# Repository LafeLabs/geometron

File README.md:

# Geometron: Geometric Metalanguage

Geometron finally gets its own space on here, since it's clearly a separate project now from Action Geometry.  Many bifurcations need to happen now to make it clearer which project is which and what the applications are.  

Geometron is a language of glyphs, which describe geometric concepts which can be interpreted both by humans and machines.  It is intended to be universally applicable across all human cultures and languages and also across all physical machine architectures both present and future.  

The political and philosophical goal of Geometron is to eliminate layers in technology which are currently controlled by various priest classes, freeing technology and giving people more power over their machines.  

This is part of the larger system of knowledge I am building, which includes the Roctal system for physical data encoding, the Action Geometry system of physical constructions, Trash Magic philosophy and technology and art, and several other components.  So all the various commands in the instruction set that this language is built on as well as the more complex components which are built up recursively have octal addresses which can be expressed using Roctal.  

### [0. Motivation Introduction](markdown/markdown_paper.md)

### [0.01 General Language Structure](what_exactly_is_geometron.md)

### [1. Fourfold Symmetry Introduction](4fold1/fourfold_symmetry.md)

### [2. Glyph of Glyphs](glyph_of_glyphs/glyph_of_glyphs.md)

### [3. Recursion: A. Square](recursionSquare/recursionSquare.md)

### [4. Scaling by 2: Halving and Doubling](scaling_by_two/scaling_by_two.md)

### [5. Angle Bisection and Scaling by Square Root of 2](square_root_2/square_root_2.md)

### [6. Glyph to Text, Text to Glyph](keyboardMapping/keyboardmapping.md)

### [7. Spelling: Glyph and Glyph Table Creation](glyphTableEdit/glyphTableEdit.md)

### [Meta-Company](meta-company.md)

### 8. Threefold and Sixfold Symmetries

### 9. Fivefold Symmetries

### 10. Detailed Study of Address Space and Roctal Encoding

### 11. Font Creation and Use

### State Stack

### 12. Adding the Third Dimension

### 13. Image Interaction for Art and Communication

### image stack

### 14. Building Systems and Implementation

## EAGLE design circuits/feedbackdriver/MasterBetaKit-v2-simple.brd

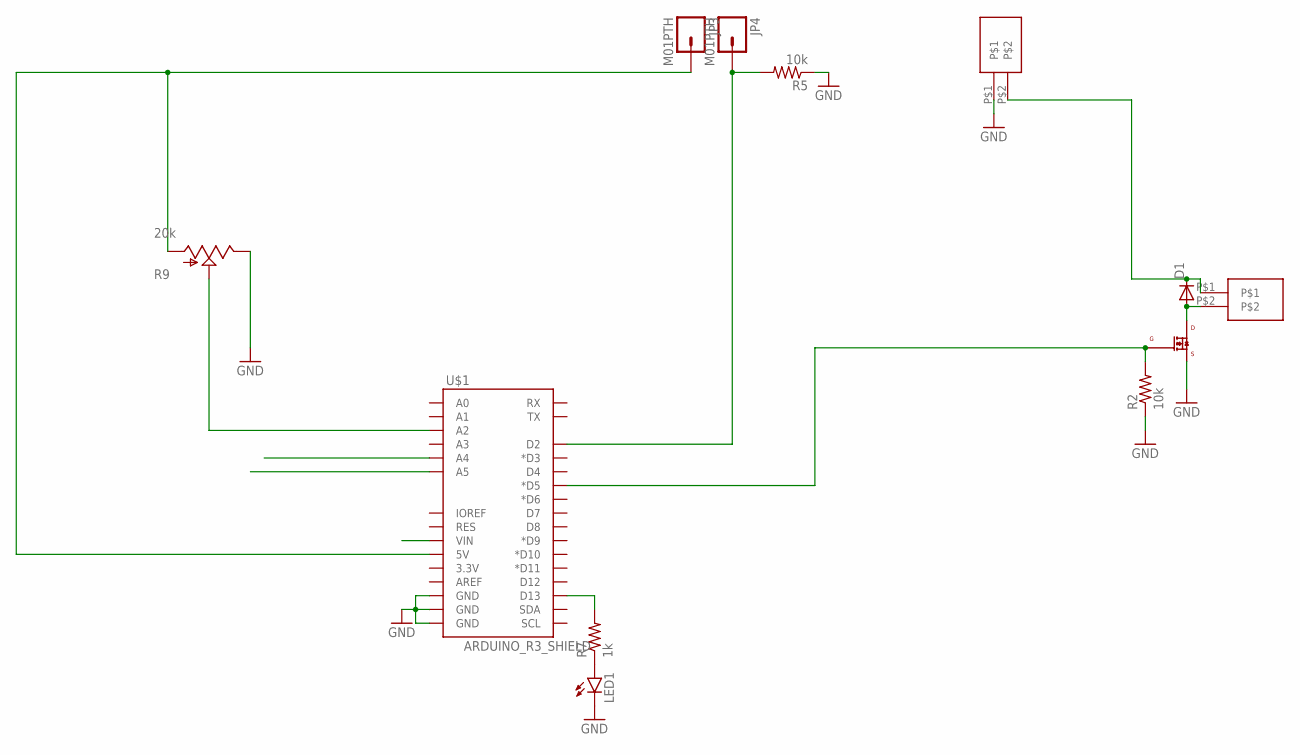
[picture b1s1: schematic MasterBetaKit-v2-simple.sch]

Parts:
D1: DIODE-DO-214AC; DO-214AC
JP3, JP4: M01PTH; 1X01
LED1: LED-3MM-NO_SILK; LED3MM-NS
R2, R5: 10k; R0603
R7: 1k; R0603
R9: 20k; ALPS_POT_KIT
U$1: ARDUINO_R3_SHIELD; UNO_R3_SHIELD
U$2: IRLML0060; SOT-23
U$6: SPRING-TERMINAL
X3: SPRING-TERMINAL

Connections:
5V: JP3.1, R9.P$3 (A), U$1.5V
BUTTON: JP4.1, R5.2, U$1.D2
CL: U$1.A5
DA: U$1.A4
GND: LED1.K (C), R2.1, R5.1, R9.P$1 (E), U$1.GND@0 (GND), U$1.GND@1 (GND), U$1.GND@2 (GND), U$2.2 (SOURCE), X3.P$1
unnamed: R2.2, U$1.D5 (*D5), U$2.1 (GATE)
unnamed: D1.A, U$2.3 (DRAIN), U$6.P$2
unnamed: LED1.A, R7.1
unnamed: R7.2, U$1.D13
unnamed: R9.P$2 (S), U$1.A2
X4: D1.C, U$6.P$1, X3.P$2

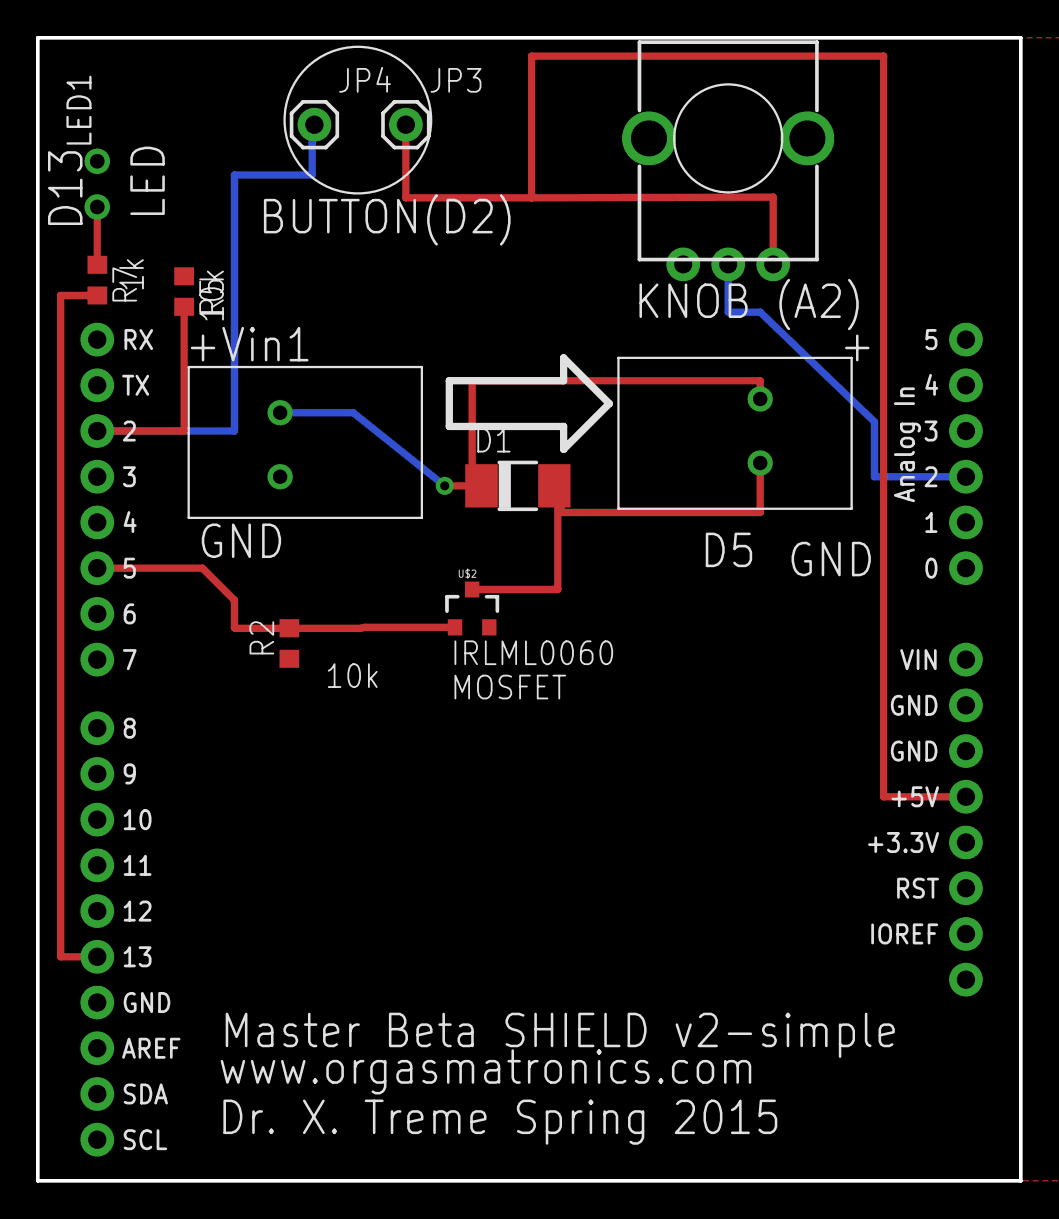
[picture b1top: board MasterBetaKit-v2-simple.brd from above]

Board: 2 copper layers, 54.6 x 63.5 mm, 12 parts (0 on the bottom side), 9 nets.

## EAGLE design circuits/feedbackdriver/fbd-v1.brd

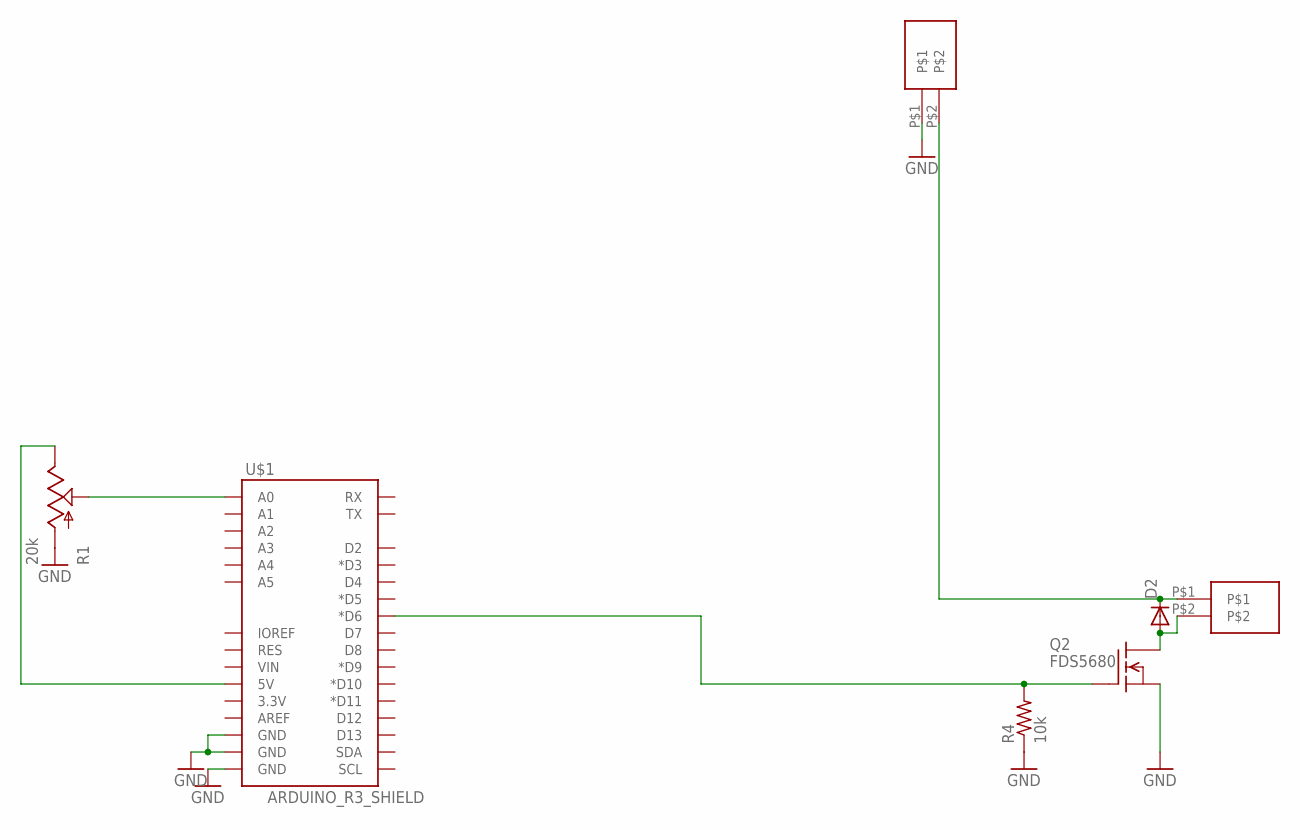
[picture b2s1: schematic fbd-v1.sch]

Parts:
D2: DIODE-DO-214AC; DO-214AC
Q2: FDS5680; SO-8
R1: 20k; ALPS_POT_KIT
R4: 10k; R0603
U$1: ARDUINO_R3_SHIELD; UNO_R3_SHIELD
X3, X5: SPRING-TERMINAL

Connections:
GND: Q2.1 (S), Q2.2 (S), Q2.3 (S), R1.P$3 (A), R4.1, U$1.GND@0 (GND), U$1.GND@1 (GND), U$1.GND@2 (GND), X3.P$1
unnamed: R1.P$2 (S), U$1.A0
unnamed: R1.P$1 (E), U$1.5V
unnamed: D2.A, Q2.5 (D), Q2.6 (D), Q2.7 (D), Q2.8 (D), X5.P$2
unnamed: Q2.4 (G), R4.2, U$1.D6 (*D6)
X4: D2.C, X3.P$2, X5.P$1

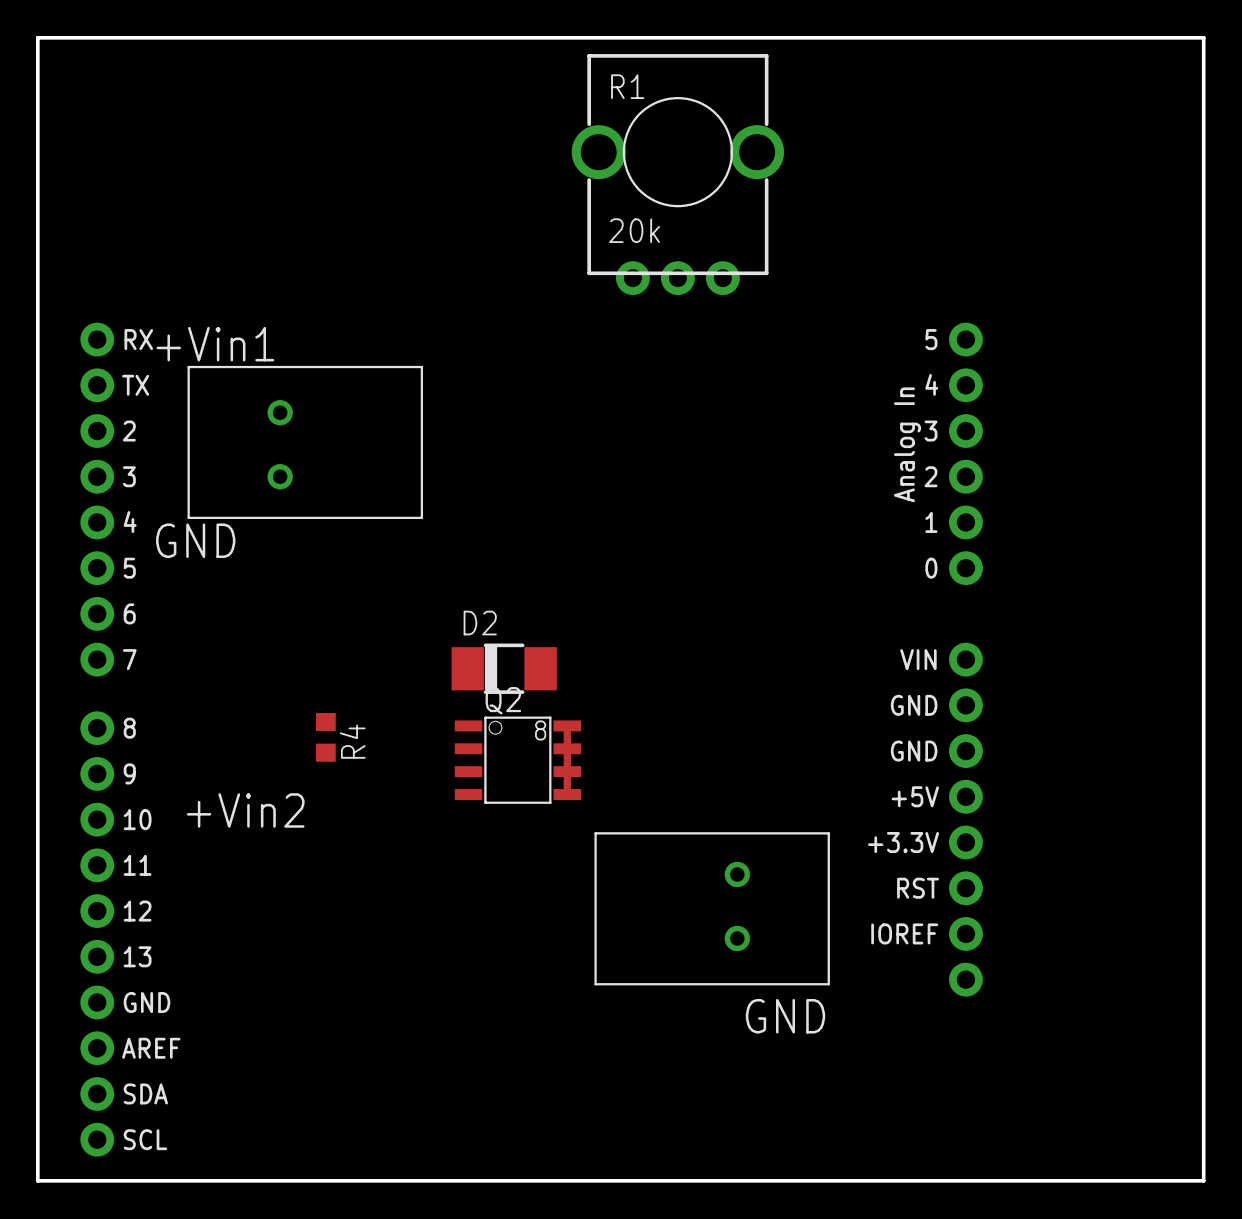
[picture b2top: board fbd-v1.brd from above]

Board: 2 copper layers, 64.8 x 63.5 mm, 7 parts (0 on the bottom side), 6 nets.

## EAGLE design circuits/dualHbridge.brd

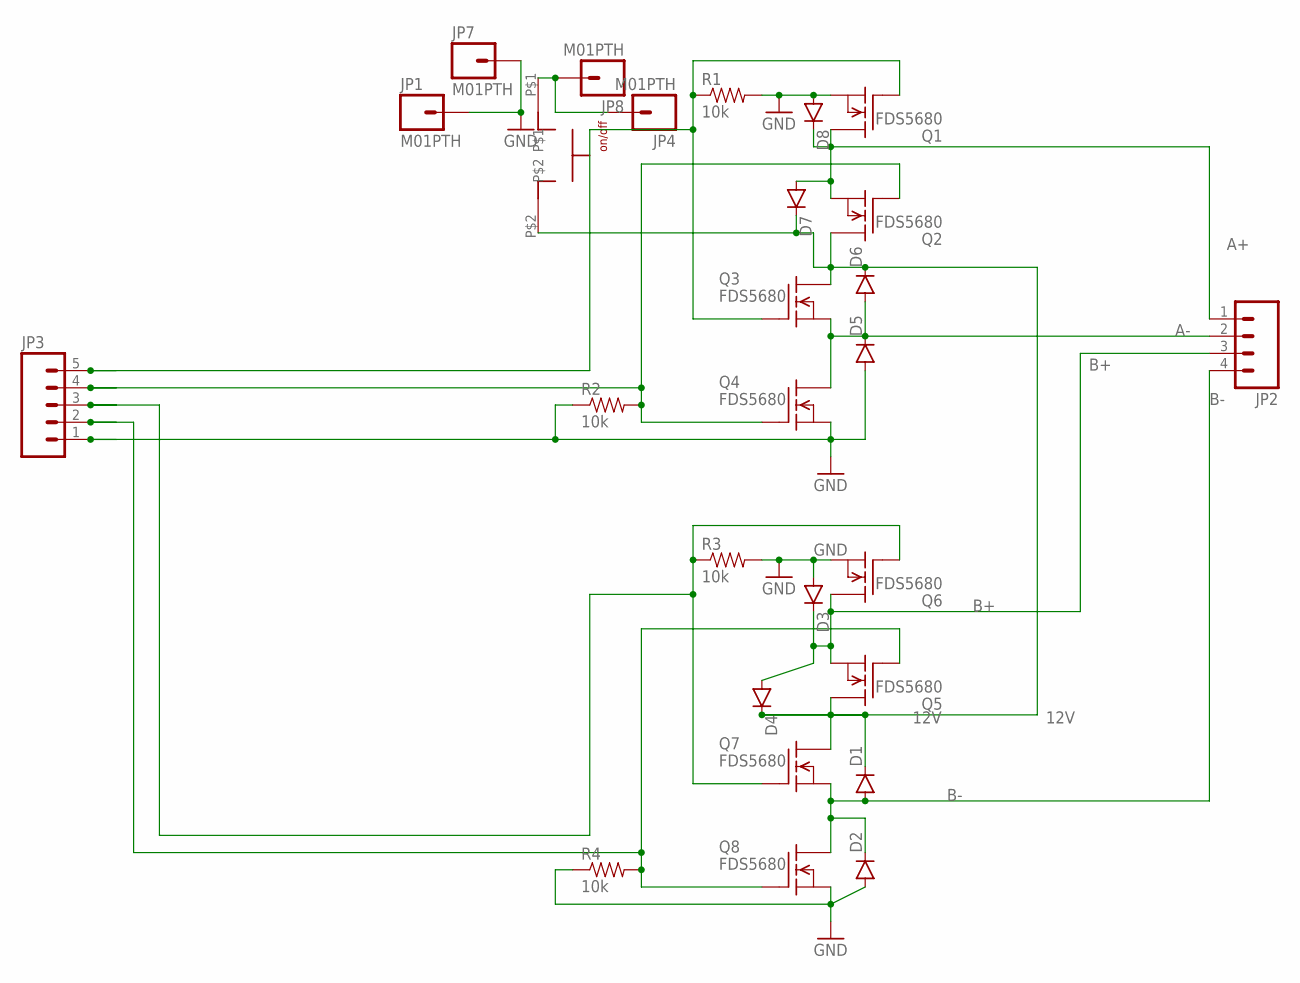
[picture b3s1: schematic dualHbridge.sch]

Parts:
D1, D2, D3, D4, D5, D6, D7, D8: DIODEKIT2; DIODE-1N4001-KIT
JP1, JP4, JP7, JP8: M01PTH; 1X01
JP2: M04LONGPADS; 1X04_LONGPADS
JP3: M05PTH; 1X05
Q1, Q2, Q3, Q4, Q5, Q6, Q7, Q8: FDS5680; SO-8
R1, R2, R3, R4: 10k; 0603-RES
U$5: CW182-ND

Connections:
12V: D1.C, D4.C, D6.C, D7.C, Q2.5 (D), Q2.6 (D), Q2.7 (D), Q2.8 (D), Q3.5 (D), Q3.6 (D), Q3.7 (D), Q3.8 (D), Q5.5 (D), Q5.6 (D), Q5.7 (D), Q5.8 (D), Q7.5 (D), Q7.6 (D), Q7.7 (D), Q7.8 (D), U$5.P$2; also elsewhere on the board
A+: D7.A, D8.C, JP2.1, Q1.5 (D), Q1.6 (D), Q1.7 (D), Q1.8 (D), Q2.1 (S), Q2.2 (S), Q2.3 (S)
A-: D5.C, D6.A, JP2.2, Q3.1 (S), Q3.2 (S), Q3.3 (S), Q4.5 (D), Q4.6 (D), Q4.7 (D), Q4.8 (D)
B+: D3.C, D4.A, JP2.3, Q5.1 (S), Q5.2 (S), Q5.3 (S), Q6.5 (D), Q6.6 (D), Q6.7 (D), Q6.8 (D)
B-: D1.A, D2.C, JP2.4, Q7.1 (S), Q7.2 (S), Q7.3 (S), Q8.5 (D), Q8.6 (D), Q8.7 (D), Q8.8 (D)
GND: D2.A, D3.A, D5.A, D8.A, JP1.1, JP3.1, JP7.1, Q1.1 (S), Q1.2 (S), Q1.3 (S), Q4.1 (S), Q4.2 (S), Q4.3 (S), Q6.1 (S), Q6.2 (S), Q6.3 (S), Q8.1 (S), Q8.2 (S), Q8.3 (S), R1.2, R2.1, R3.2, R4.1; also elsewhere on the board
unnamed: JP3.5, Q1.4 (G), Q3.4 (G), R1.1
unnamed: JP3.4, Q2.4 (G), Q4.4 (G), R2.2
unnamed: JP3.3, Q6.4 (G), Q7.4 (G), R3.1
unnamed: JP3.2, Q5.4 (G), Q8.4 (G), R4.2
unnamed 14: JP4.1, JP8.1, U$5.P$1; also elsewhere on the board

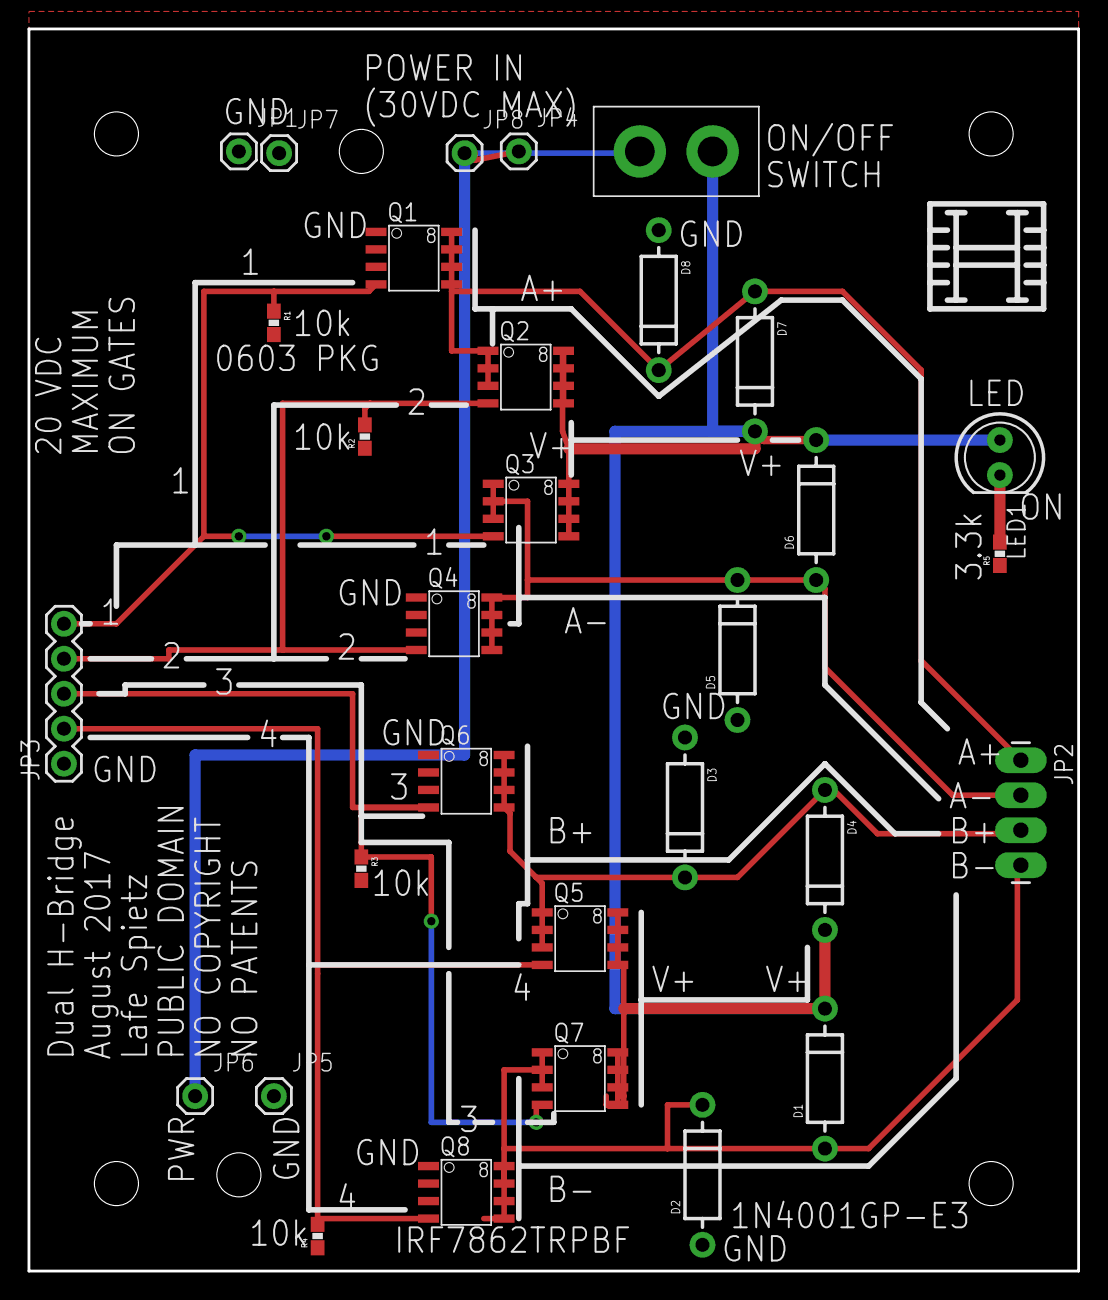
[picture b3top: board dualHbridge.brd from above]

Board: 2 copper layers, 76.2 x 90.2 mm, 31 parts (0 on the bottom side), 12 nets.

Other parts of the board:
JP5, JP6: M01PTH; 1X01
LED1: LED5MM
R5: 3.3k; 0603-RES

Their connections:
12V: LED1.A; also elsewhere on the board
GND: JP5.1, R5.1; also elsewhere on the board
unnamed: LED1.K, R5.2
unnamed 14: JP6.1; also elsewhere on the board

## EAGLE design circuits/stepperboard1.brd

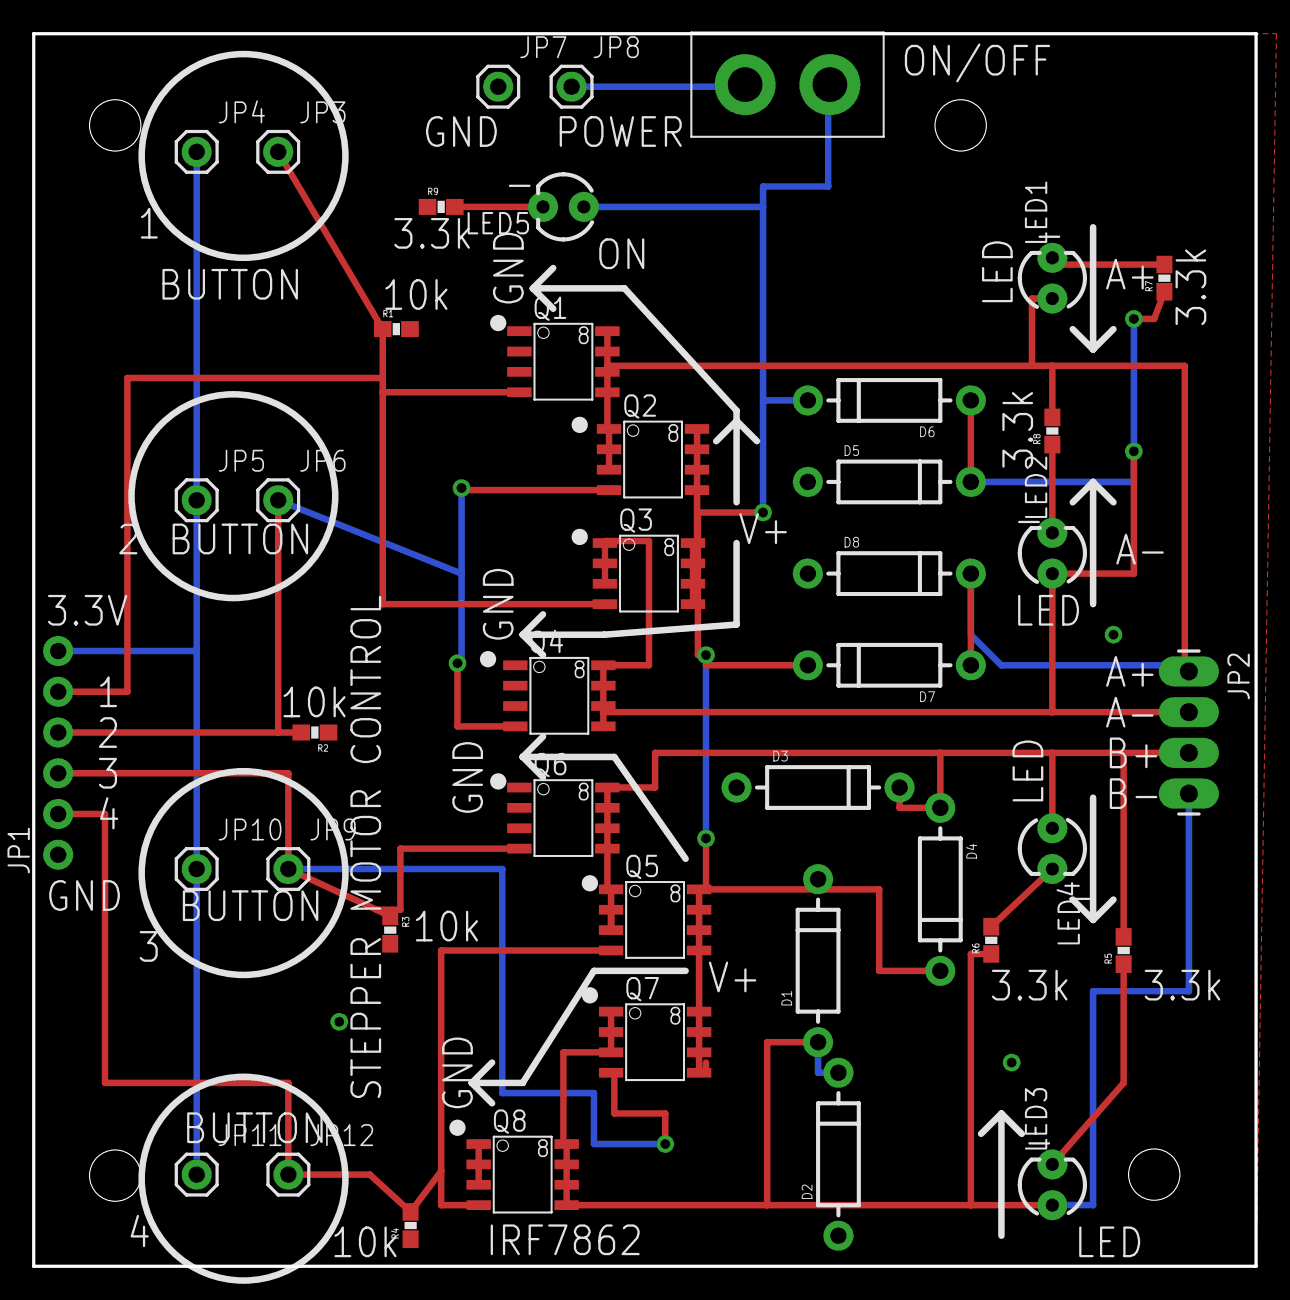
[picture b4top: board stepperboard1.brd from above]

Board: 2 copper layers, 76.2 x 76.8 mm, 43 parts (0 on the bottom side), 17 nets.

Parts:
D1, D2, D3, D4, D5, D6, D7, D8: DIODE-1N4001-KIT
JP1: 1X06_NO_SILK
JP2: 1X04_LONGPADS
JP3, JP4, JP5, JP6, JP7, JP8, JP9, JP10, JP11, JP12: M01PTH; 1X01
LED1, LED2, LED3, LED4, LED5: LED3MM
Q1, Q2, Q3, Q4, Q5, Q6, Q7, Q8: FDS5680; SO-8
R1, R2, R3, R4: 10k; 0603-RES
R5, R6, R7, R8, R9: 3.3k; 0603-RES
U$5: CW182-ND

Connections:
12V: D1.C, D4.C, D6.C, D7.C, LED5.A, Q2.5, Q2.6, Q2.7, Q2.8, Q3.5, Q3.6, Q3.7, Q3.8, Q5.5, Q5.6, Q5.7, Q5.8, Q7.5, Q7.6, Q7.7, Q7.8, U$5.P$2
A+: D7.A, D8.C, JP2.1, LED1.A, Q1.5, Q1.6, Q1.7, Q1.8, Q2.1, Q2.2, Q2.3, R8.2
A-: D5.C, D6.A, JP2.2, LED2.A, Q3.1, Q3.2, Q3.3, Q4.5, Q4.6, Q4.7, Q4.8, R7.1
B+: D3.C, D4.A, JP2.3, LED4.A, Q5.1, Q5.2, Q5.3, Q6.5, Q6.6, Q6.7, Q6.8, R5.2
B-: D1.A, D2.C, JP2.4, LED3.A, Q7.1, Q7.2, Q7.3, Q8.5, Q8.6, Q8.7, Q8.8, R6.1
GND: D2.A, D3.A, D5.A, D8.A, JP1.1, JP7.1, Q1.1, Q1.2, Q1.3, Q4.1, Q4.2, Q4.3, Q6.1, Q6.2, Q6.3, Q8.1, Q8.2, Q8.3, R1.2, R2.1, R3.2, R4.1, R9.1
unnamed: LED1.K, R7.2
unnamed: JP1.5, JP3.1, Q1.4, Q3.4, R1.1
unnamed: JP1.4, JP6.1, Q2.4, Q4.4, R2.2
unnamed: LED2.K, R8.1
unnamed: LED3.K, R5.1
unnamed: LED4.K, R6.2
unnamed: JP1.3, JP9.1, Q6.4, Q7.4, R3.1
unnamed: JP1.2, JP12.1, Q5.4, Q8.4, R4.2
unnamed: JP8.1, U$5.P$1
unnamed: LED5.K, R9.2
V3.3: JP1.6, JP4.1, JP5.1, JP10.1, JP11.1

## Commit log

2016-12-20 read me fleshed out a bit
2016-12-20 writing a actual document on fourfold symmetry
2016-12-20 added standalone app for just moving cursor, documented it
2016-12-20 added link from read me to fourfold section
2016-12-20 finished a draft of fourfold symmetry section
2016-12-20 added links to code at the end
2016-12-20 fixed directory name in link
2016-12-20 made links work properly connected it all together with read
2016-12-20 glyph of glyphs section mostly done
2016-12-20 added many sections to read me to be filled out next
2016-12-20 added doubling stuff and finished draft of recursion section
2016-12-20 not even sure what happened woke from nap
2016-12-21 added license
2016-12-21 added sqrt(2) stuff
2016-12-21 root 2 mostly done but need a ton more examples and explanation of the math
2016-12-22 added to keyboard mapping section, sketched out Root Magic Table
2016-12-22 clarified address bullet list with more ALL CAPS
2016-12-23 putting font together, finished 0300s table
2016-12-23 shape tables and font now done, ready for next step
2016-12-24 going from integer arrays to text works, but keyboard mode needs work, thought
2016-12-24 dropped the variable currentGlyph[] completely, using currentGlyphString for all, WORKS!!!!
2016-12-25 I can now edit a manuscript! The whole system appears to work now.
2016-12-25 made some more neat stuff in "manuscript"
2016-12-28 played with shapes, made new shapes, updated key map graphics
2016-12-29 ascii table ready to print
2016-12-29 cartoons explaining cursor in printable pdf
2016-12-30 scroll is a document to document itself, now has keys on spelling
2016-12-30 standalone app works now with geometron intro book--scroll1
2016-12-30 moved stuff around started mapping
2016-12-31 crowd funding strategy document
2017-01-01 image table works position stack works, root magic works
2017-01-01 ROOT MAGIC APOCALYPSE
2017-01-02 more documentation as art
2017-01-02 added timestamp to screenshot saver and more docs to function doc
2017-01-02 longbridgepark
2017-01-02 more documentation of octal, roctal
2017-01-03 an actual distribution for other people
2017-01-04 played with logarithmic spirals based on different generators
2017-01-05 crowd fund plan, more random bits
2017-01-05 updated ascii table to have roctal
2017-01-05 made pdfs with roctal youtube url stubs to be filled in by hand after printing
2017-01-06 read laminated code, links successfuly to youtube
2017-01-07 added some ideas on crowd fund
2017-01-07 printable scannable roctal codes for tale and lore for root2spiral tablet
2017-01-12 random tiny updates
2017-01-12 storyboarded the video
2017-01-14 more on video plans
2017-01-15 arduino control of trash robot
2017-01-20 added roctal code for geometron javascript page
2017-01-20 added a html sandbox to geometron repository
2017-01-21 made a js library and it works! i can now attempt to communicate with "normals"
2017-01-21 using processing to convert text to other text
2017-01-29 xml super apocalypse
    rewriting the entire geometron system in xml, attempting to break free
    of specific computer languages, fix stupid ascii problems i had
2017-01-29 xml is a fucking pile of steaming shit
    after 24 hours wasted on xml it is clear this solves no problems and
    adds several. going back to .txt in all cases
2017-01-29 xml is a piece of shit, moving back to all txt
    xml solves minimal issues and adds many, is clearly shit
2017-01-30 converted to txt then from txt to js, put that in library
2017-01-31 added manual conversion from text commands to octal commands
2017-03-20 Documenting the whole project in a markdown doc, not sure where to put this, need to move it somewhere
2017-03-21 moving bits around in main markdown docs
2017-03-21 updating documents on geometron pointing to the Project
2017-03-22 small tweaks here...
2017-04-23 trash2 is the current trash printer control code
2017-04-28 code updated for trash printer
2017-04-30 working on the crowd fund
2017-04-30 working on crowd fund video script
2017-05-16 successfully ported geometron into python! all with .SVG format output
2017-05-17 python geometron is now really working
2017-05-18 total recursion!!!!!
2017-05-18 fixed tab in textarea
2017-06-02 working with python to improve work flow with byte code and libraries
2017-06-03 from js to byte code
2017-06-04 more work on python encapsulation of byte code
2017-06-11 creator work in python
2017-06-12 this server side nonsense is working now
2017-06-15 more hypercube structure, more python, etc
2017-06-17 learning tons of css and getting whole new glyph editor paradigm online with css
2017-07-13 tons of things, plotting etc
2017-07-17 phone gap
2017-07-18 native app stuff, and arrow table updates
2017-07-20 cube6 is the next big evolution in overall structure
2017-07-24 some cube shit
2017-07-25 lots of map and plot stuff
2017-07-30 made a circuit board stepper thingy best H bridge ever
2017-08-02 h bridge circuit board
2017-08-10 repeated attempts to make gerber files that work
2017-08-18 css robotics experiments, new keyboard mapping html file
2017-08-23 circuit layout stuff
2017-08-31 robots
2017-09-01 dual stepper control code

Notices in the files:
circuits/dualHbridge.brd:
PUBLIC DOMAIN
circuits/feedbackdriver/MasterBetaKit-v2-simple.brd:
Open Hardware Creative Commons License
circuits/stepperboard1.brd:
NO COPYRIGHTS
parts and their libraries:
SparkFun-Aesthetics: Licensing: Creative Commons ShareAlike 4.0 International - https://creativecommons.org/licenses/by-sa/4.0
